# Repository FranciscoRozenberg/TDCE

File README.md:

Proyecto Integrador para cursada de Taller de Circuitos Electrónicos - 2C2026 - FIUBA

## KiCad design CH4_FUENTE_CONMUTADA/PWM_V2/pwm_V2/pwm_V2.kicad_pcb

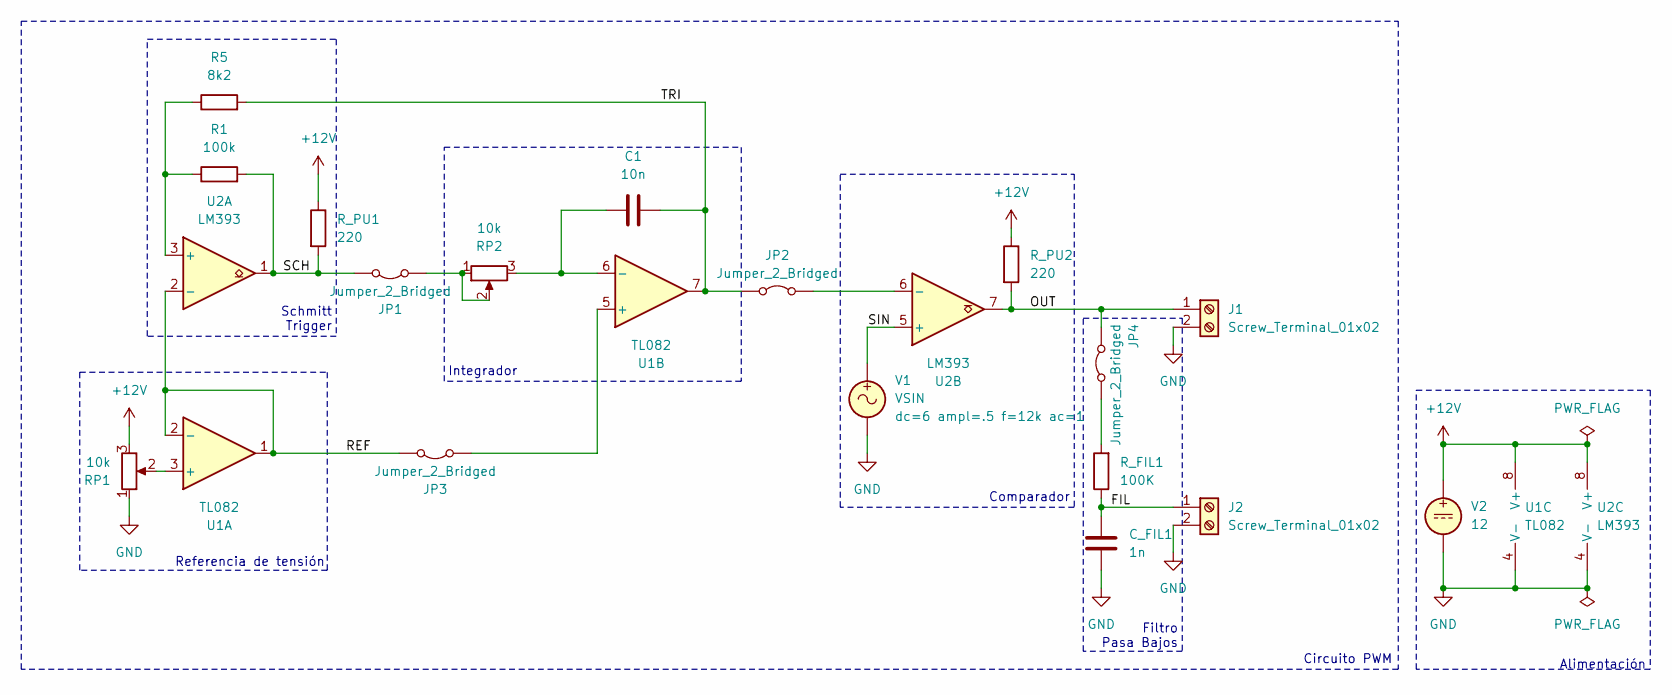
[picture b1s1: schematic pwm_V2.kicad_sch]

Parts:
C1: 10n; C_Disc_D10.0mm_W2.5mm_P5.00mm
C_FIL1: 1n; C_Disc_D10.0mm_W2.5mm_P5.00mm
J1, J2: Screw_Terminal_01x02; TerminalBlock_MaiXu_MX126-5.0-02P_1x02_P5.00mm
JP1, JP2, JP3, JP4: Jumper_2_Bridged; TestPoint_2Pads_Pitch2.54mm_Drill0.8mm
R1: 100k; R_Axial_DIN0207_L6.3mm_D2.5mm_P10.16mm_Horizontal
R5: 8k2; R_Axial_DIN0207_L6.3mm_D2.5mm_P10.16mm_Horizontal
RP1, RP2: 10k; Potentiometer_Alps_RK163_Single_Horizontal
R_FIL1: 100K; R_Axial_DIN0207_L6.3mm_D2.5mm_P10.16mm_Horizontal
R_PU1, R_PU2: 220; R_Axial_DIN0207_L6.3mm_D2.5mm_P10.16mm_Horizontal
U1: TL082; DIP-8_W7.62mm_LongPads
U2: LM393; DIP-8_W7.62mm_LongPads
V1: VSIN; TerminalBlock_MaiXu_MX126-5.0-02P_1x02_P5.00mm
V2: 12; TerminalBlock_MaiXu_MX126-5.0-02P_1x02_P5.00mm

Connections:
+12V: RP1.3, R_PU1.1, R_PU2.1, U1.8 (V+), U2.8 (V+), V2.1
/FIL: C_FIL1.1, J2.1, R_FIL1.1
/OUT: J1.1, JP4.2 (B), R_PU2.2, U2.7
/REF: JP3.1 (A), U1.1, U1.2 (-), U2.2 (-)
/SCH: JP1.1 (A), R1.2, R_PU1.2, U2.1
/SIN: U2.5 (+), V1.1
/TRI: C1.2, JP2.1 (A), R5.2, U1.7
GND: C_FIL1.2, J1.2, J2.2, RP1.1, U1.4 (V-), U2.4 (V-), V1.2, V2.2
unnamed: JP1.2 (B), RP2.1, RP2.2
unnamed: JP2.2 (B), U2.6 (-)
unnamed: JP3.2 (B), U1.5 (+)
unnamed: JP4.1 (A), R_FIL1.2
unnamed: RP1.2, U1.3 (+)
unnamed: C1.1, RP2.3, U1.6 (-)
unnamed: R1.1, R5.1, U2.3 (+)

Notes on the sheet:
Integrador
Referencia de tensión
Schmitt Trigger
Filtro Pasa Bajos
Alimentación
Circuito PWM
Comparador

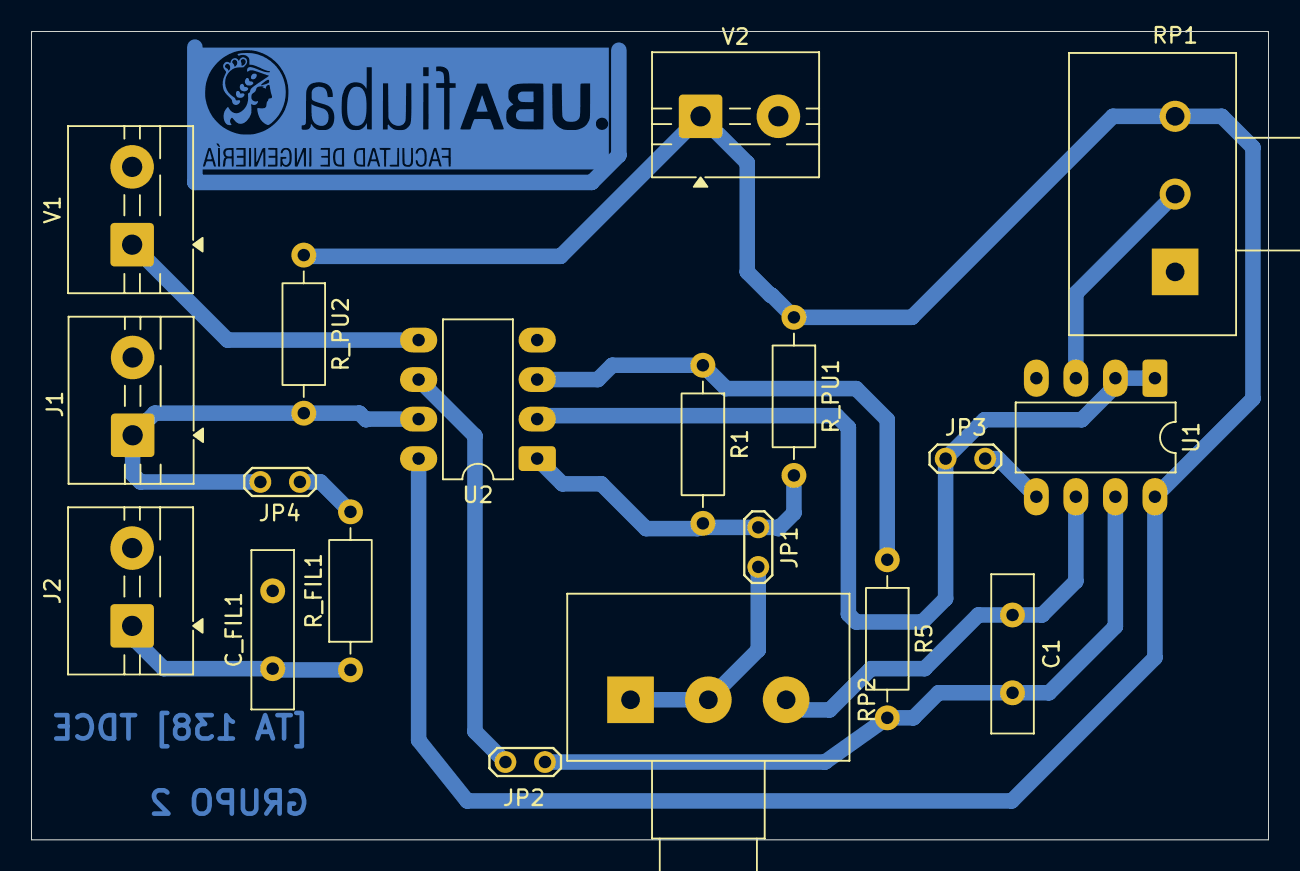
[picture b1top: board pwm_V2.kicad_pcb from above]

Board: 2 copper layers, 79.5 x 52.0 mm, 19 parts (0 on the bottom side), 15 nets.

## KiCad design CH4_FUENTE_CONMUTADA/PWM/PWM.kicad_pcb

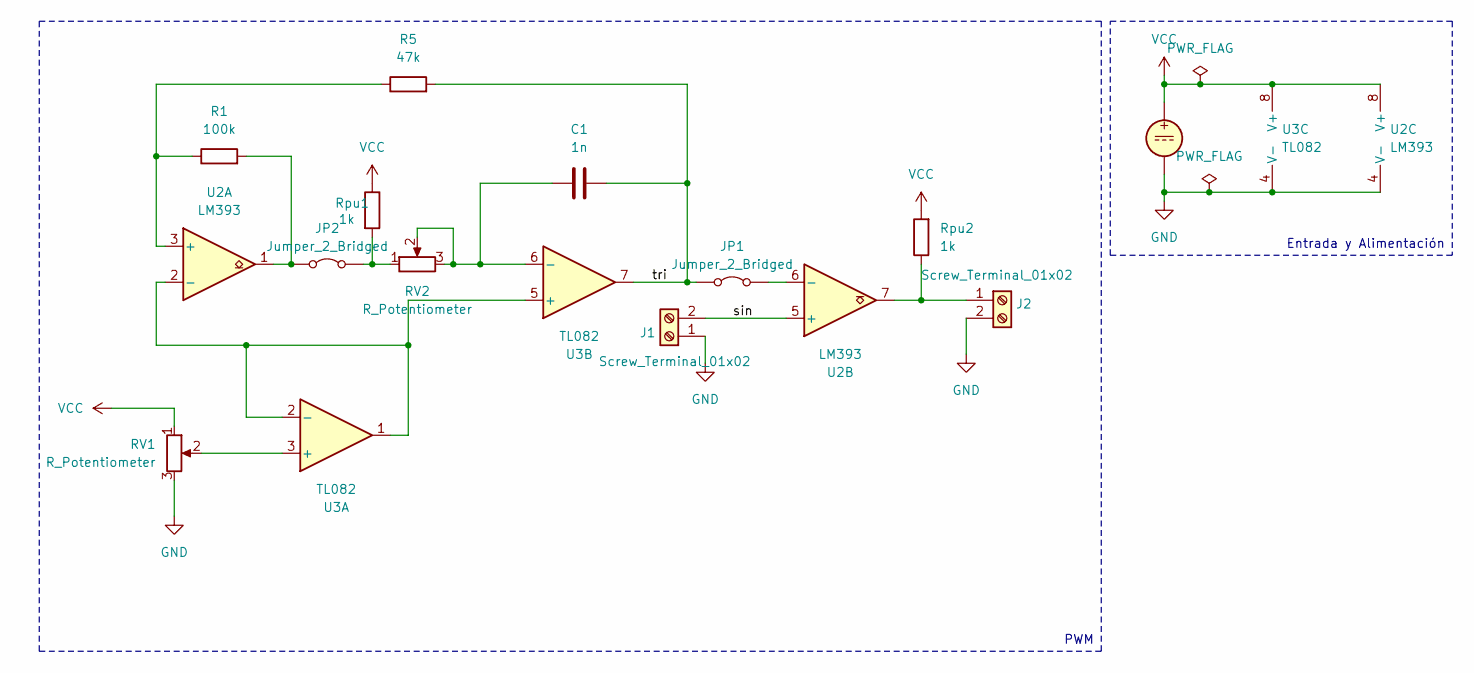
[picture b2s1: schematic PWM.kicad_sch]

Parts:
C1: 1n; C_Disc_D10.0mm_W2.5mm_P5.00mm
J1, J2: Screw_Terminal_01x02; TerminalBlock_MaiXu_MX126-5.0-02P_1x02_P5.00mm
JP1, JP2: Jumper_2_Bridged; TestPoint_2Pads_Pitch2.54mm_Drill0.8mm
R1: 100k; R_Axial_DIN0207_L6.3mm_D2.5mm_P10.16mm_Horizontal
R5: 47k; R_Axial_DIN0207_L6.3mm_D2.5mm_P10.16mm_Horizontal
RV1, RV2: R_Potentiometer; Potentiometer_Bourns_3296W_Vertical
Rpu1, Rpu2: 1k; R_Axial_DIN0207_L6.3mm_D2.5mm_P10.16mm_Horizontal
U2: LM393; DIP-8_W7.62mm_Socket
U3: TL082; DIP-8_W7.62mm_LongPads
V1: 12; TerminalBlock_MaiXu_MX126-5.0-02P_1x02_P5.00mm

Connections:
/sin: J1.2, U2.5 (+)
/tri: C1.2, JP1.1 (A), R5.2, U3.7
GND: J1.1, J2.2, RV1.3, U2.4 (V-), U3.4 (V-), V1.2
unnamed: J2.1, Rpu2.1, U2.7
unnamed: JP1.2 (B), U2.6 (-)
unnamed: JP2.1 (A), R1.2, U2.1
unnamed: JP2.2 (B), RV2.1, Rpu1.2
unnamed: R1.1, R5.1, U2.3 (+)
unnamed: U2.2 (-), U3.1, U3.2 (-), U3.5 (+)
unnamed: RV1.2, U3.3 (+)
unnamed: C1.1, RV2.2, RV2.3, U3.6 (-)
VCC: RV1.1, Rpu1.1, Rpu2.2, U2.8 (V+), U3.8 (V+), V1.1

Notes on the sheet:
PWM
Entrada y Alimentación

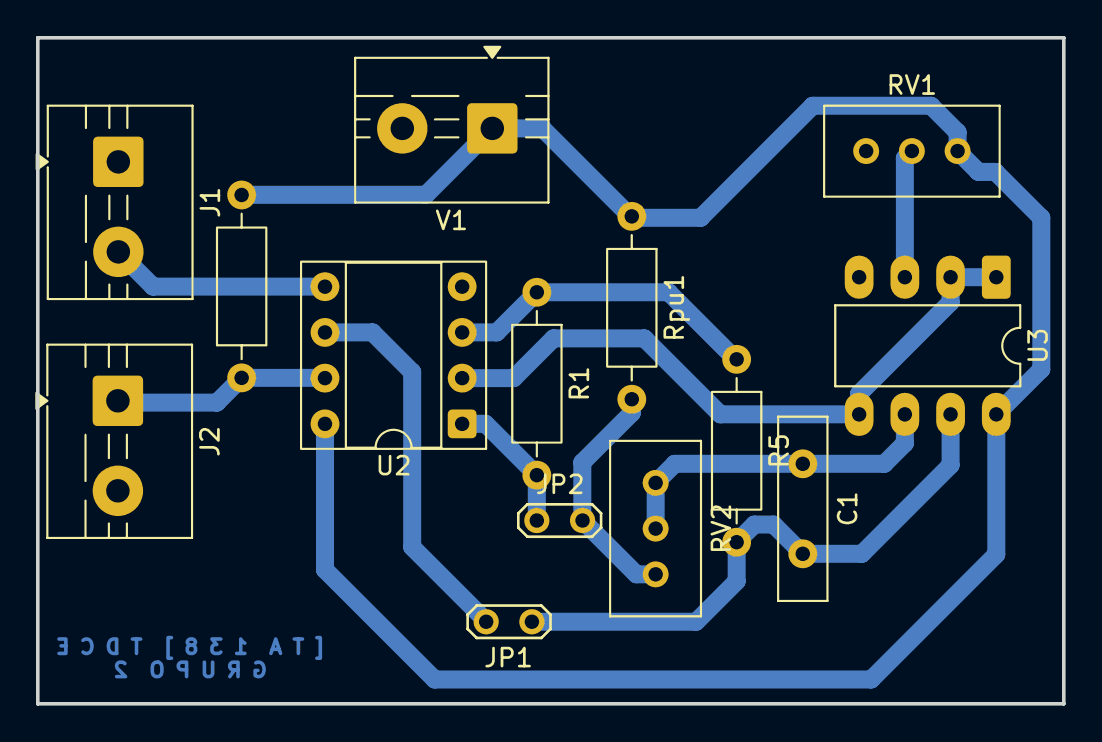
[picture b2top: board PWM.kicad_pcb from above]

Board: 2 copper layers, 57.0 x 37.0 mm, 14 parts (0 on the bottom side), 12 nets.

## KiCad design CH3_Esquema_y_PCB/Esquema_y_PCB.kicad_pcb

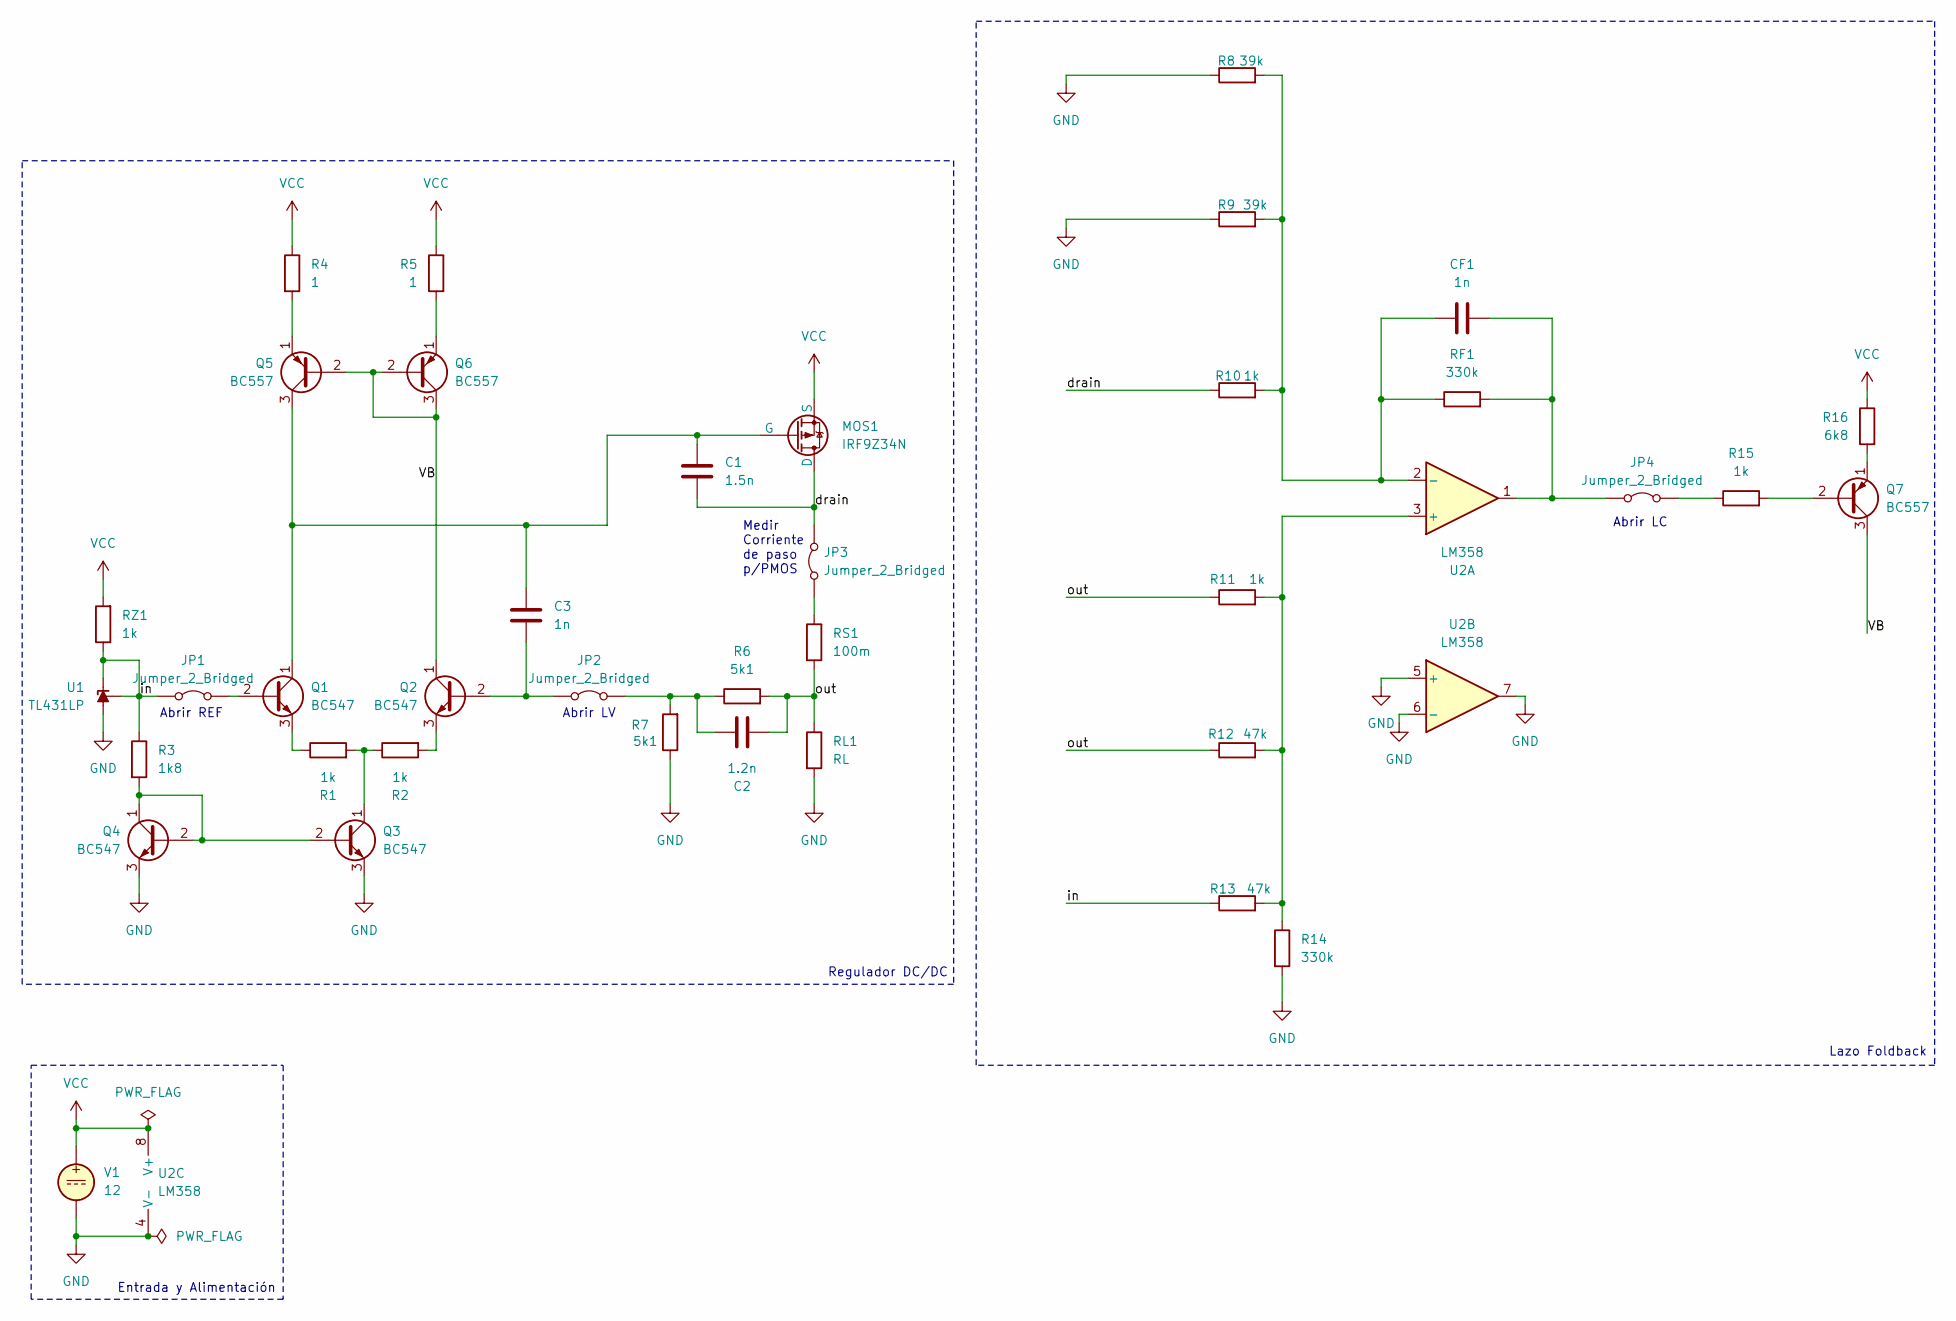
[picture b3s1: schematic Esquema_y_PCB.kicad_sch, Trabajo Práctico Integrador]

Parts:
C1: 1.5n; C_Disc_D5.0mm_W2.5mm_P5.00mm
C2: 1.2n; C_Disc_D7.5mm_W5.0mm_P7.50mm
C3: 1n; C_Disc_D5.0mm_W2.5mm_P5.00mm
CF1: 1n; C_Disc_D5.0mm_W2.5mm_P5.00mm
JP1, JP2, JP3, JP4: Jumper_2_Bridged; TestPoint_2Pads_Pitch2.54mm_Drill0.8mm
MOS1: IRF9Z34N; TO-220-3_Vertical
Q1, Q2, Q3, Q4: BC547; TO-92_Wide
Q5, Q6, Q7: BC557; TO-92_Wide
R1, R2, R10, R11, R15: 1k; R_Axial_DIN0207_L6.3mm_D2.5mm_P10.16mm_Horizontal
R3: 1k8; R_Axial_DIN0207_L6.3mm_D2.5mm_P10.16mm_Horizontal
R4, R5: 1; R_Axial_DIN0207_L6.3mm_D2.5mm_P10.16mm_Horizontal
R6, R7: 5k1; R_Axial_DIN0207_L6.3mm_D2.5mm_P10.16mm_Horizontal
R8, R9: 39k; R_Axial_DIN0207_L6.3mm_D2.5mm_P10.16mm_Horizontal
R12: 47k; R_Axial_DIN0207_L6.3mm_D2.5mm_P10.16mm_Horizontal
R13: 47k; R_Axial_DIN0207_L6.3mm_D2.5mm_P15.24mm_Horizontal
R14: 330k; R_Axial_DIN0207_L6.3mm_D2.5mm_P10.16mm_Horizontal
R16: 6k8; R_Axial_DIN0207_L6.3mm_D2.5mm_P10.16mm_Horizontal
RF1: 330k; R_Axial_DIN0207_L6.3mm_D2.5mm_P10.16mm_Horizontal
RL1: RL; TerminalBlock_MaiXu_MX126-5.0-02P_1x02_P5.00mm
RS1: 100m; R_Axial_Power_L20.0mm_W6.4mm_P25.40mm
RZ1: 1k; R_Axial_DIN0207_L6.3mm_D2.5mm_P10.16mm_Horizontal
U1: TL431LP; TO-92_Wide
U2: LM358; DIP-8_W7.62mm_Socket_LongPads
V1: 12; TerminalBlock_MaiXu_MX126-5.0-02P_1x02_P5.00mm

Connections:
/VB: Q2.1 (C), Q5.2 (B), Q6.2 (B), Q6.3 (C), Q7.3 (C)
/drain: C1.2, JP3.2 (B), MOS1.2 (D), R10.1
/in: JP1.1 (A), R3.1, R13.1, RZ1.1, U1.1 (REF), U1.3 (K)
/out: C2.2, R6.2, R11.1, R12.1, RL1.1, RS1.2
GND: Q3.3 (E), Q4.3 (E), R7.1, R8.1, R9.1, R14.2, RL1.2, U1.2 (A), U2.4 (V-), U2.5 (+), U2.6 (-), U2.7, V1.2
unnamed: JP1.2 (B), Q1.2 (B)
unnamed: C3.2, JP2.1 (A), Q2.2 (B)
unnamed: C2.1, JP2.2 (B), R6.1, R7.2
unnamed: JP3.1 (A), RS1.1
unnamed: CF1.2, JP4.1 (A), RF1.2, U2.1
unnamed: JP4.2 (B), R15.1
unnamed: C1.1, C3.1, MOS1.1 (G), Q1.1 (C), Q5.3 (C)
unnamed: Q1.3 (E), R1.1
unnamed: Q2.3 (E), R2.2
unnamed: Q3.2 (B), Q4.1 (C), Q4.2 (B), R3.2
unnamed: Q3.1 (C), R1.2, R2.1
unnamed: Q5.1 (E), R4.2
unnamed: Q6.1 (E), R5.2
unnamed: Q7.2 (B), R15.2
unnamed: Q7.1 (E), R16.2
unnamed: R11.2, R12.2, R13.2, R14.1, U2.3 (+)
unnamed: CF1.1, R8.2, R9.2, R10.2, RF1.1, U2.2 (-)
VCC: MOS1.3 (S), R4.1, R5.1, R16.1, RZ1.2, U2.8 (V+), V1.1

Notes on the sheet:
Abrir LV
Medir Corriente de paso p/PMOS
Abrir REF
Lazo Foldback
Regulador DC/DC
Abrir LC
Entrada y Alimentación

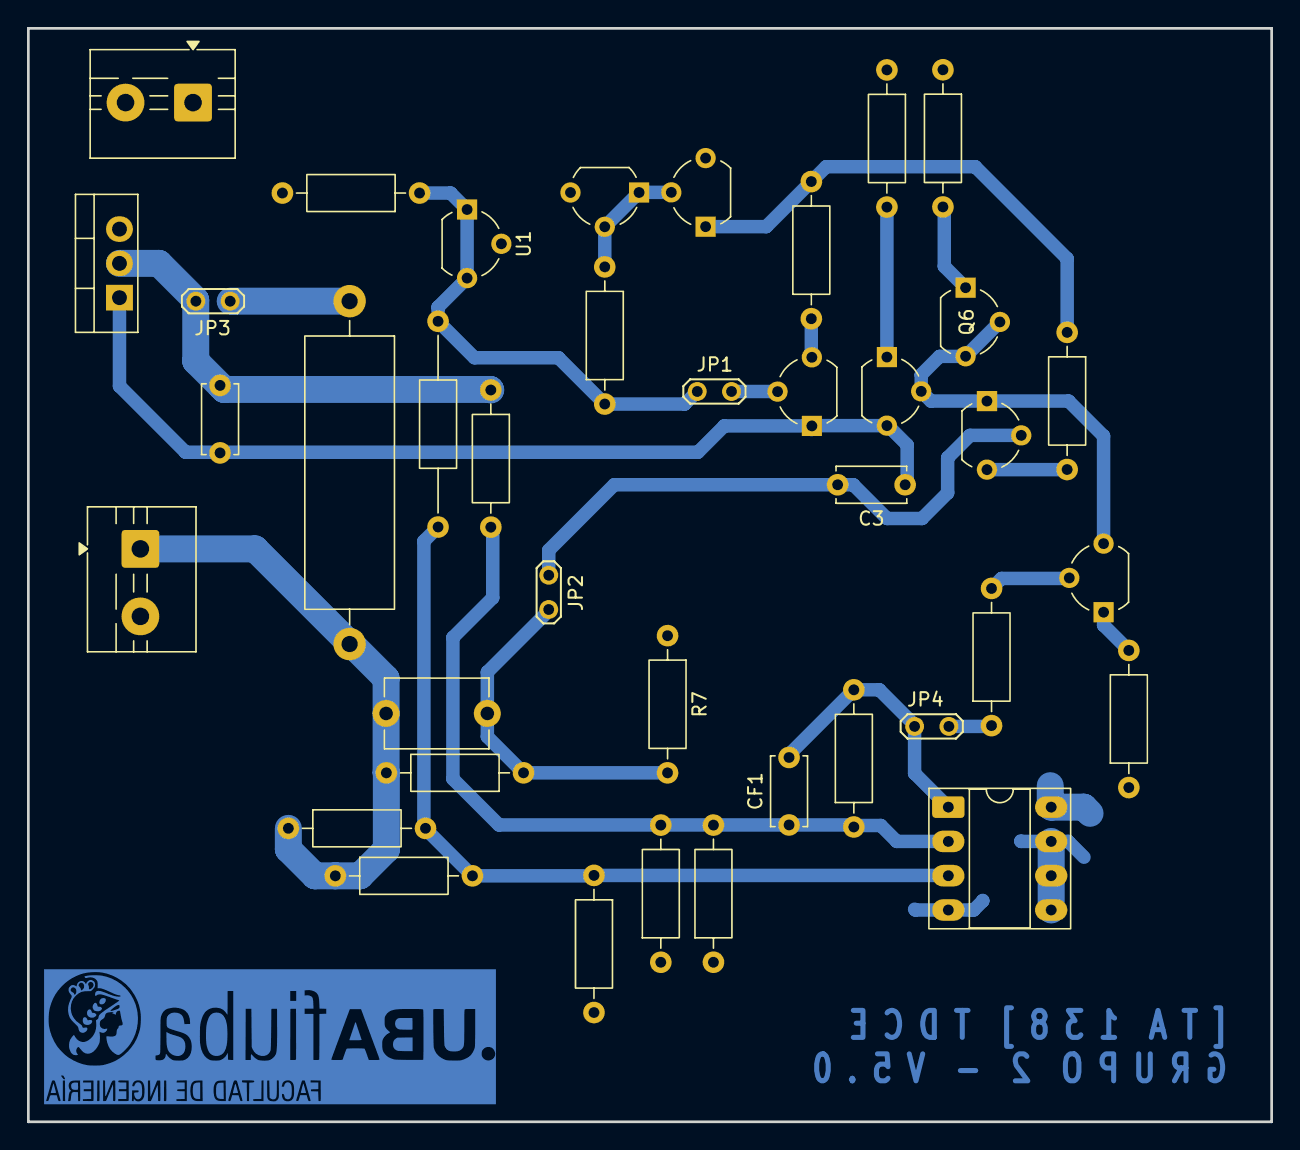
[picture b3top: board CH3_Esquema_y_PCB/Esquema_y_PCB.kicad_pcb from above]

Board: 2 copper layers, 92.1 x 81.0 mm, 39 parts (0 on the bottom side), 23 nets.

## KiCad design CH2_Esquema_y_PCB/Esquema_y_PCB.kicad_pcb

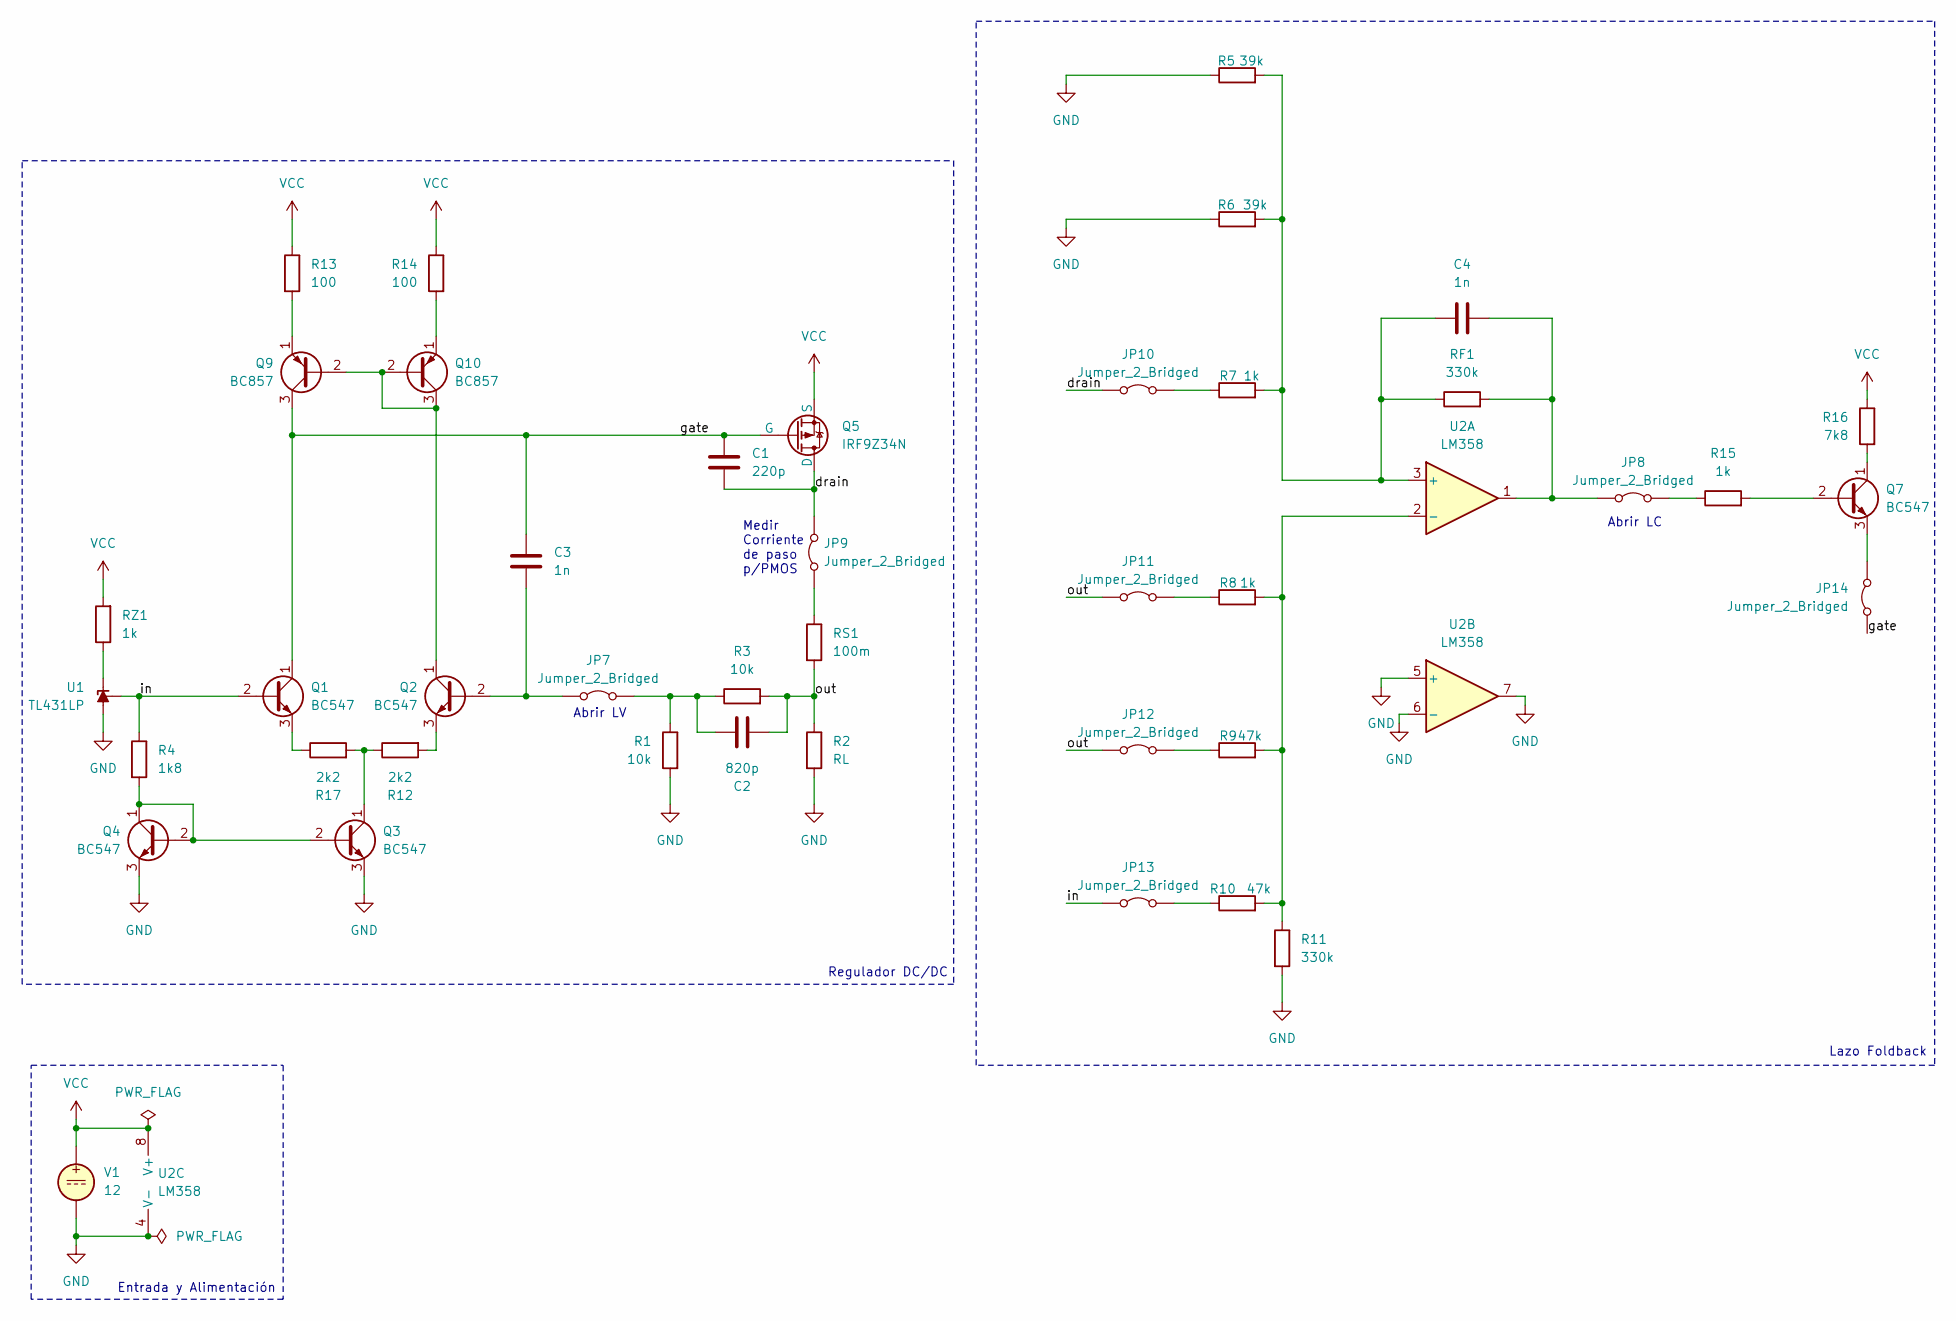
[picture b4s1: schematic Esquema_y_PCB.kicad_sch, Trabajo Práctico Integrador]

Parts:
C1: 220p; C_Disc_D5.0mm_W2.5mm_P5.00mm
C2: 820p; C_Disc_D7.5mm_W5.0mm_P7.50mm
C3: 1n; C_Disc_D7.5mm_W5.0mm_P7.50mm
C4: 1n; C_Disc_D5.0mm_W2.5mm_P5.00mm
JP7, JP8, JP9, JP10, JP11, JP12, JP13, JP14: Jumper_2_Bridged; TestPoint_2Pads_Pitch2.54mm_Drill0.8mm
Q1, Q2, Q3, Q4, Q7: BC547; TO-92_Wide
Q5: IRF9Z34N; TO-220-3_Vertical
Q9, Q10: BC857; TO-92_Wide
R1, R3: 10k; R_Axial_DIN0207_L6.3mm_D2.5mm_P10.16mm_Horizontal
R2: RL; TerminalBlock_MaiXu_MX126-5.0-02P_1x02_P5.00mm
R4: 1k8; R_Axial_DIN0207_L6.3mm_D2.5mm_P10.16mm_Horizontal
R5, R6: 39k; R_Axial_DIN0207_L6.3mm_D2.5mm_P10.16mm_Horizontal
R7, R8, R15: 1k; R_Axial_DIN0207_L6.3mm_D2.5mm_P10.16mm_Horizontal
R9, R10: 47k; R_Axial_DIN0207_L6.3mm_D2.5mm_P10.16mm_Horizontal
R11: 330k; R_Axial_DIN0207_L6.3mm_D2.5mm_P10.16mm_Horizontal
R12, R17: 2k2; R_Axial_DIN0207_L6.3mm_D2.5mm_P10.16mm_Horizontal
R13, R14: 100; R_Axial_DIN0207_L6.3mm_D2.5mm_P10.16mm_Horizontal
R16: 7k8; R_Axial_DIN0207_L6.3mm_D2.5mm_P10.16mm_Horizontal
RF1: 330k; R_Axial_DIN0207_L6.3mm_D2.5mm_P10.16mm_Horizontal
RS1: 100m; R_Axial_Power_L20.0mm_W6.4mm_P25.40mm
RZ1: 1k; R_Axial_DIN0207_L6.3mm_D2.5mm_P10.16mm_Horizontal
U1: TL431LP; TO-92_Wide
U2: LM358; DIP-8_W7.62mm_Socket_LongPads
V1: 12; TerminalBlock_MaiXu_MX126-5.0-02P_1x02_P5.00mm

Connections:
/drain: C1.2, JP9.2 (B), JP10.1 (A), Q5.2 (D)
/gate: C1.1, C3.1, JP14.2 (B), Q1.1 (C), Q5.1 (G), Q9.3 (C)
/in: JP13.1 (A), Q1.2 (B), R4.1, U1.1 (REF)
/out: C2.2, JP11.1 (A), JP12.1 (A), R2.1, R3.2, RS1.2
GND: Q3.3 (E), Q4.3 (E), R1.2, R2.2, R5.1, R6.1, R11.2, U1.2 (A), U2.4 (V-), U2.5 (+), U2.6 (-), U2.7, V1.2
unnamed: C3.2, JP7.1 (A), Q2.2 (B)
unnamed: C2.1, JP7.2 (B), R1.1, R3.1
unnamed: C4.2, JP8.1 (A), RF1.2, U2.1
unnamed: JP8.2 (B), R15.1
unnamed: JP9.1 (A), RS1.1
unnamed: JP10.2 (B), R7.1
unnamed: JP11.2 (B), R8.1
unnamed: JP12.2 (B), R9.1
unnamed: JP13.2 (B), R10.1
unnamed: JP14.1 (A), Q7.3 (E)
unnamed: Q1.3 (E), R17.1
unnamed: Q2.3 (E), R12.2
unnamed: Q3.2 (B), Q4.1 (C), Q4.2 (B), R4.2
unnamed: Q3.1 (C), R12.1, R17.2
unnamed: Q7.2 (B), R15.2
unnamed: Q7.1 (C), R16.2
unnamed: Q9.1 (E), R13.2
unnamed: Q2.1 (C), Q9.2 (B), Q10.2 (B), Q10.3 (C)
unnamed: Q10.1 (E), R14.2
unnamed: RZ1.1, U1.3 (K)
unnamed: C4.1, R5.2, R6.2, R7.2, RF1.1, U2.3 (+)
unnamed: R8.2, R9.2, R10.2, R11.1, U2.2 (-)
VCC: Q5.3 (S), R13.1, R14.1, R16.1, RZ1.2, U2.8 (V+), V1.1

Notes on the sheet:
Abrir LV
Medir Corriente de paso p/PMOS
Lazo Foldback
Regulador DC/DC
Abrir LC
Entrada y Alimentación

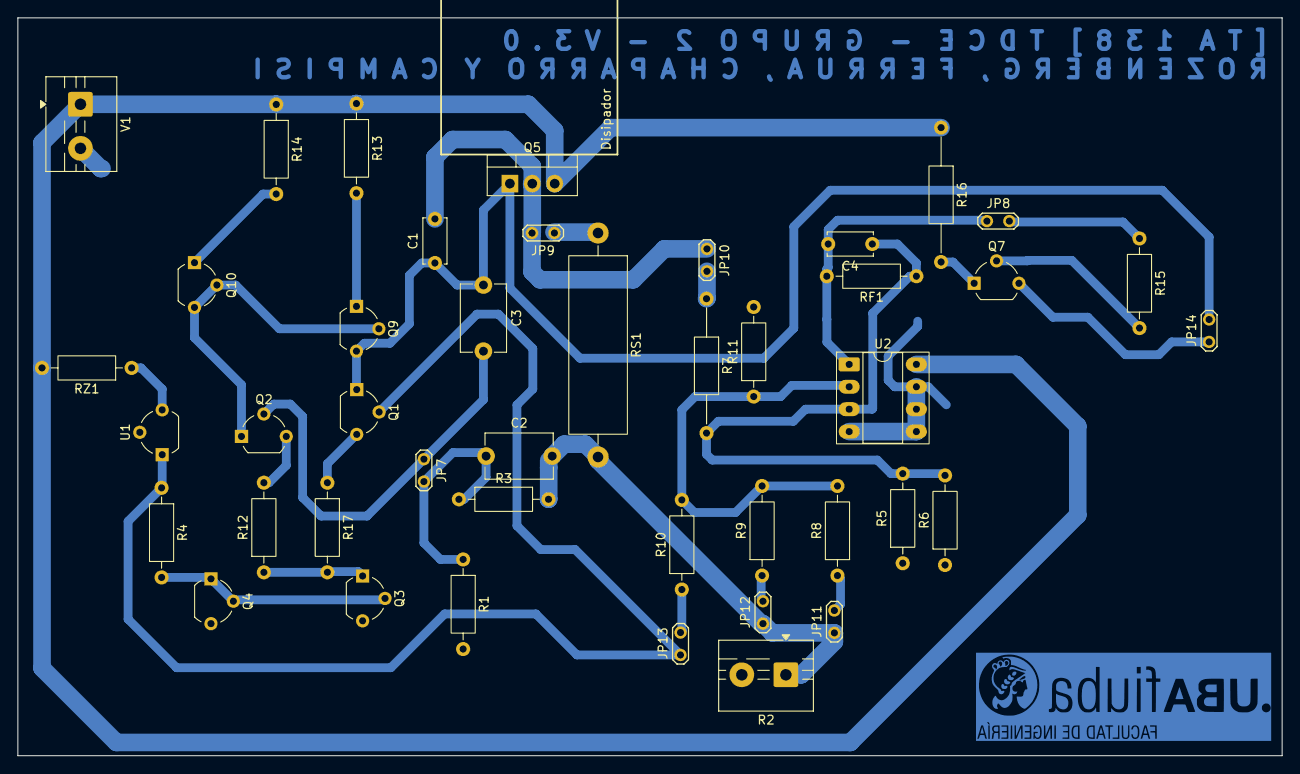
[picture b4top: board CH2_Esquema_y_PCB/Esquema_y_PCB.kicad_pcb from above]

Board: 2 copper layers, 143.4 x 83.7 mm, 43 parts (0 on the bottom side), 28 nets.

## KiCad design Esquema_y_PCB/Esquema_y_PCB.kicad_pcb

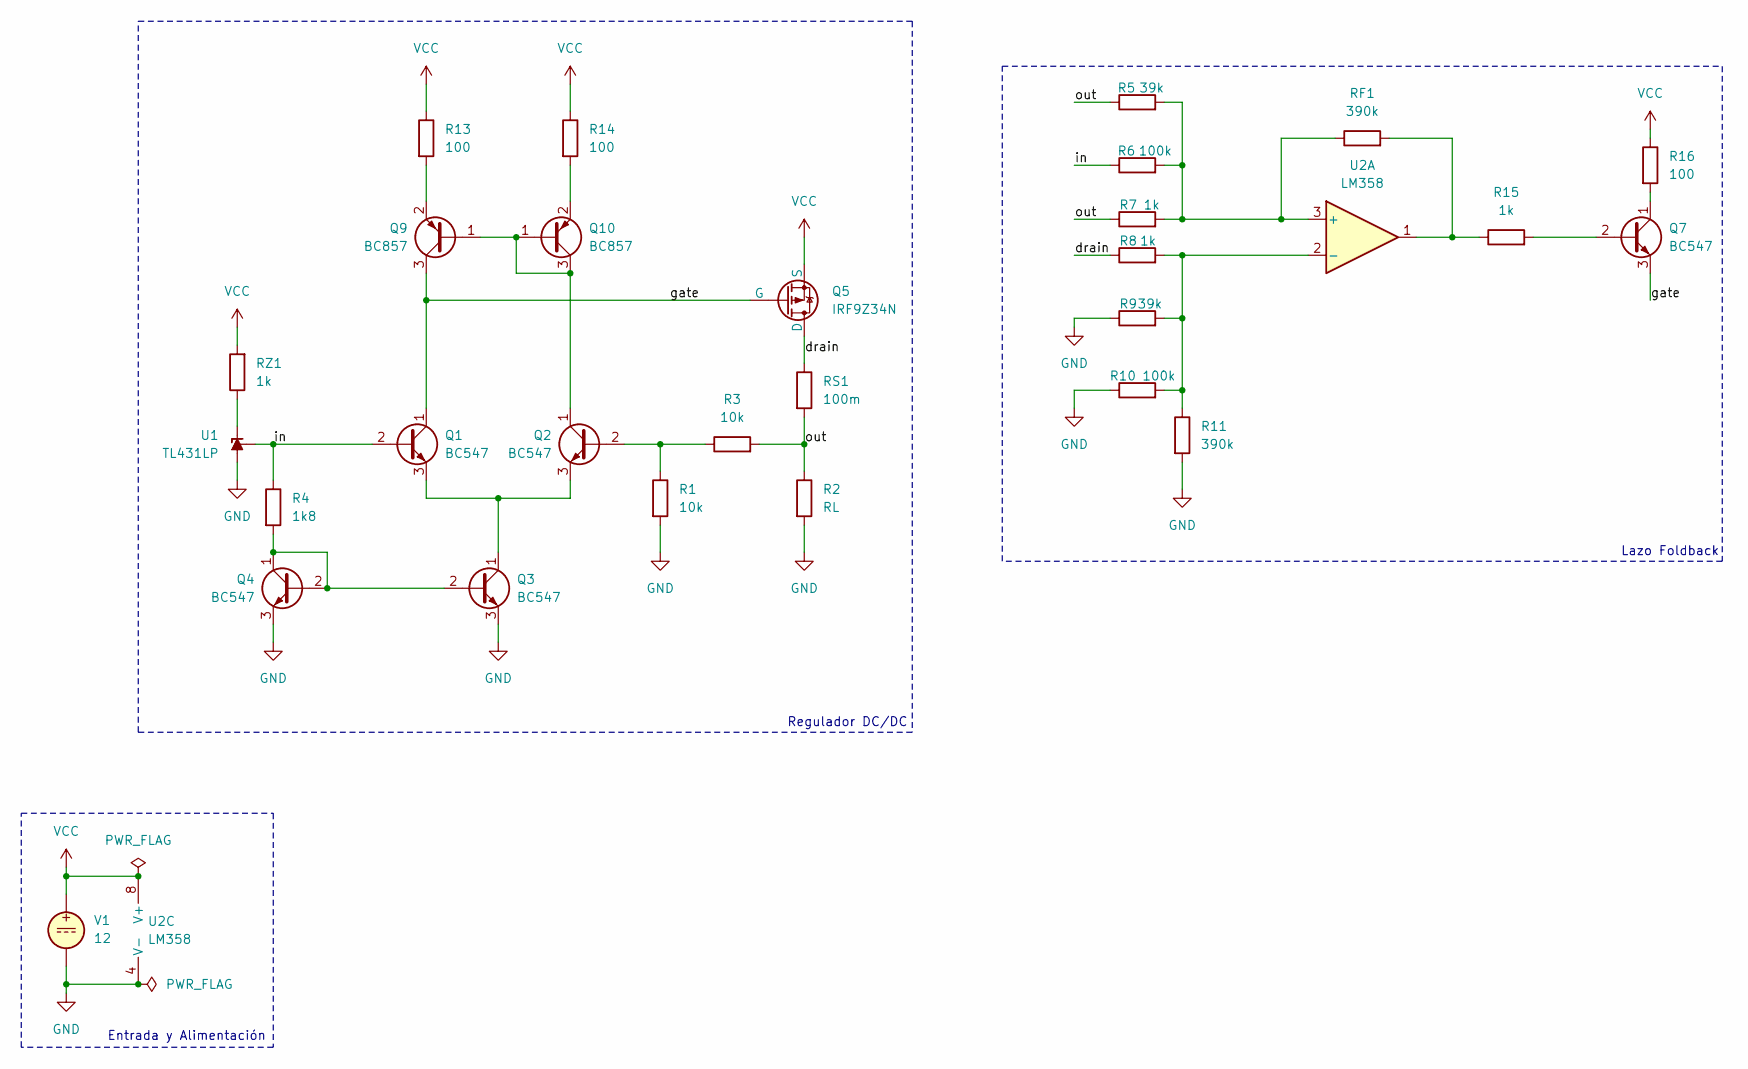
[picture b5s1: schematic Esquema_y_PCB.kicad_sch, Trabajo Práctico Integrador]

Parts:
Q1, Q2, Q3, Q4, Q7: BC547; TO-92_Inline
Q5: IRF9Z34N; TO-220-3_Vertical
Q9, Q10: BC857; TO-92_Inline
R1, R3: 10k; R_Axial_DIN0204_L3.6mm_D1.6mm_P5.08mm_Horizontal
R2: RL; TerminalBlock_MaiXu_MX126-5.0-02P_1x02_P5.00mm
R4: 1k8; R_Axial_DIN0204_L3.6mm_D1.6mm_P5.08mm_Horizontal
R5, R9: 39k; R_Axial_DIN0204_L3.6mm_D1.6mm_P5.08mm_Horizontal
R6, R10: 100k; R_Axial_DIN0204_L3.6mm_D1.6mm_P5.08mm_Horizontal
R7, R8, R15: 1k; R_Axial_DIN0204_L3.6mm_D1.6mm_P5.08mm_Horizontal
R11: 390k; R_Axial_DIN0204_L3.6mm_D1.6mm_P5.08mm_Horizontal
R13, R14, R16: 100; R_Axial_DIN0204_L3.6mm_D1.6mm_P5.08mm_Horizontal
RF1: 390k; R_Axial_DIN0204_L3.6mm_D1.6mm_P5.08mm_Horizontal
RS1: 100m; R_Axial_DIN0414_L11.9mm_D4.5mm_P15.24mm_Horizontal
RZ1: 1k; R_Axial_DIN0204_L3.6mm_D1.6mm_P5.08mm_Horizontal
U1: TL431LP; TO-92_Inline
U2: LM358; DIP-8_W7.62mm_Socket_LongPads
V1: 12; TerminalBlock_MaiXu_MX126-5.0-02P_1x02_P5.00mm

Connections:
/drain: Q5.1 (D), R8.1, RS1.1
/gate: Q1.1 (C), Q5.2 (G), Q7.3 (E), Q9.3 (C)
/in: Q1.2 (B), R4.1, R6.1, U1.1 (REF)
/out: R2.1, R3.2, R5.1, R7.1, RS1.2
GND: Q3.3 (E), Q4.3 (E), R1.2, R2.2, R9.1, R10.1, R11.2, U1.2 (A), U2.4 (V-), V1.2
unnamed: Q1.3 (E), Q2.3 (E), Q3.1 (C)
unnamed: Q2.2 (B), R1.1, R3.1
unnamed: Q3.2 (B), Q4.1 (C), Q4.2 (B), R4.2
unnamed: Q7.2 (B), R15.2
unnamed: Q7.1 (C), R16.2
unnamed: Q9.2 (E), R13.2
unnamed: Q2.1 (C), Q9.1 (B), Q10.1 (B), Q10.3 (C)
unnamed: Q10.2 (E), R14.2
unnamed: R15.1, RF1.2, U2.1
unnamed: RZ1.1, U1.3 (K)
unnamed: R5.2, R6.2, R7.2, RF1.1, U2.3 (+)
unnamed: R8.2, R9.2, R10.2, R11.1, U2.2 (-)
VCC: Q5.3 (S), R13.1, R14.1, R16.1, RZ1.2, U2.8 (V+), V1.1

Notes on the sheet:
Lazo Foldback
Regulador DC/DC
Entrada y Alimentación

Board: 2 copper layers, 29 parts (0 on the bottom side), 18 nets, no tracks yet.
